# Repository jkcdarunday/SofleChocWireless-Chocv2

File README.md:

# Sofle Choc Wireless — Choc v2 Hole-Only

> **Untested hardware:** This modified PCB has not been physically tested.
> File-level checks do not verify switch fit, assembly, or electrical operation.
> Fabricate and build at your own risk; a working keyboard is not guaranteed.

| Left half (back view) | Right half (front view) |
| --- | --- |
|  |  |

Green bare-board KiCad 10 renders with component models hidden, arranged as
the assembled keyboard: left half on the left, right half on the right. The
reversible PCB uses its back face for the left half and front face for the
right half. SW25 is the isolated encoder/switch position below the reset button
in the right-half view.

Based on db-ok/SofleChocWireless at
`aae7cc0ac5ca563dab8222320ae8749ed1911e56`. This branch contains the adapted
board, matching source footprints and project settings, and fabrication files.

## Changes in this version

Enlarges all 30 switch-center NPTH holes from 3.4 mm to 5.0 mm, including SW25.
Reroutes affected connections around the enlarged center holes and uses
0.25 mm ground bridges where needed. No vias were added, removed, or moved.
No additional silent-switch pin relief is included in this version.

For switches requiring an additional locating-pin slot, see the
[Choc v2 Silent v2 branch](https://github.com/jkcdarunday/SofleChocWireless-Chocv2/tree/choc-v2-silent-v2),
which adds mirrored 1.5 × 2.0 mm non-plated slots at every switch position.

Both silkscreen labels credit `jkcdarunday` and the base design by `db`.
The schematic, electrical pad mapping, component placements, outline, LED
cutouts, mounting holes, firmware mapping, and case/plate geometry are preserved.

Open `SofleChocWireless/PCB/SofleKeyboard.kicad_pro` in KiCad 7 or newer.
The 30-position main board is reversible and serves either half.
`Gerbers/SofleChocWireless/SofleChocWireless.zip` contains this version's
main-board copper, masks, silkscreens, outline, and PTH/NPTH drills; the loose
exports match the archive. Plate exports remain unchanged upstream files.

## Validation and remaining limits

Saved KiCad 7.0.11 checks reported 400 findings before and after conversion,
with zero copper clearance violations and zero unconnected pads. Later
KiCad 9 checks also found no new electrical DRC issues in the conversion;
counts differ with engine, library resolution, and zone filling.

These are historical file-level results, not a new validation run or physical
qualification. Existing DRC findings remain. At SW25, the enlarged hole leaves
only a nominal 0.249 mm laminate web to the LED cutout. Confirm fabrication
capability and the actual switch/plate fit before ordering. No physical switch
fit, assembled-board, or power/temperature tests have been performed. The RGB
power arrangement is unchanged. Original license and attribution are retained.

## Upstream documentation

# Sofle Choc Wireless Keyboard

The Sofle Choc Wireless Keyboard is a revision of the Sofle Choc keyboard by [Brian Low](https://github.com/brianlow) with features that make it more suitable to building with wireless microcontrollers.

*The Sofle Choc Wireless Keyboard with an encoder and nice!view on the left half*

--
--

The following 2 pictures are the same exact board:

  *(Above: the Sofle Choc Wireless Keyboard with RGB LEDs and dual encoders)*

  *(Above: The Sofle Choc Wireless Keyboard with RGB LEDs and no encoders)*

The encoders in the first picture were hot-swapped for Choc switches in the second picture.
This allows for more build flexibility to change up your build, and as an added bonus, you can test out different rotary encoder options without soldering them in until you find one that you like.

## Disclaimer
This is a prototype keyboard, so it comes with no guarantees. There may be changes to it in the future to fix problems or add features. That being said, it functions as intended for my own standards, so if you like the design, feel free to get a PCB made and build it for yourself!

## Differences from Sofle Choc (wired) keyboard
- Added power switch to connect/disconnect battery power to RAW pin of microcontroller
- Added JST connector for battery connection
- [nice!view](https://nicekeyboards.com/docs/nice-view/) display support *(still supports common OLED displays as well)*
- Encoder can be swapped with a Choc switch on either half
    - These can both be hot-swapped if Mill-Max sockets are installed
- Added a bottom plate PCB to allow for more build options
- Made a hole in the PCB for battery wire routing if needed
- Position of the encoder is shifted down to allow room for a larger encoder knob
- 1 additional RBG LED on each half under the encoder / choc switch position
- Removed the TRRS jacks and related components
- Changed the microcontroller pin connected to the RGB LED data line

## Encoder Support
The PCB supports a rotary encoder or a Choc switch in the same location on either half, and *either one can use Mill-Max sockets*. If you don't want to use Mill-Max sockets, you can hard-solder either a rotary encoder or a Choc switch into either side.

## Display Support
The PCB supports either a 4-pin OLED screen commonly found on DIY keyboards, or the 5-pin [nice!view](https://nicekeyboards.com/docs/nice-view/) low power usage display.

## Firmware 

Sofle Choc Wireless uses [ZMK firmware](https://zmk.dev/)

Firmware-related info for display and LED features:
  - This PCB has a chip select (CS) pin for the nice!view display that uses Arduino Digital 1 (D1 Pro Micro pin), which corresponds to P0.06/006 on the nice!nano. This is the default pin used by the nice!view, which makes it easier to configure. See build guide "Firmware and programming" section for more info on building firmware that supports the nice!view.
  - The RGB LED pin is relocated to Arduino Digital 0 (D0 Pro Micro pin), which corresponds to P0.08/008 on the nice!nano

### Example config repository
There is a zmk-config example repository where each branch has a different combination of options (OLED, niceview, RGB) enabled:
https://github.com/db-ok/zmk-config-soflechocwireless

## Build Guide

Please read the entire build guide before ordering any parts, as there are some options to consider:

[Build guide](docs/build_guide_choc_wireless.md)

## From the original Sofle repo:

Original SofleKeyboard repo: https://github.com/josefadamcik/SofleKeyboard

Sofle is 6×4+5 keys column-staggered split keyboard with encoder support. 

Based on [Lily58](https://github.com/kata0510/Lily58), [Corne](https://github.com/foostan/crkbd) and [Helix](https://github.com/MakotoKurauchi/helix) keyboards.

SofleKeyboard was created by [Josef Adamcik](https://josef-adamcik.cz/). The motivation and process is covered in following blog-post: [Let me introduce you to SofleKeyboard - a split keyboard based on Lily58 and Crkbd](https://josef-adamcik.cz/electronics/let-me-introduce-you-sofle-keyboard-split-keyboard-based-on-lily58.html)

Sofle RGB was contributed by [Dane Evans](https://github.com/DaneEvans).

Sofle Choc was designed by [Brian Low](https://github.com/BrianLow)

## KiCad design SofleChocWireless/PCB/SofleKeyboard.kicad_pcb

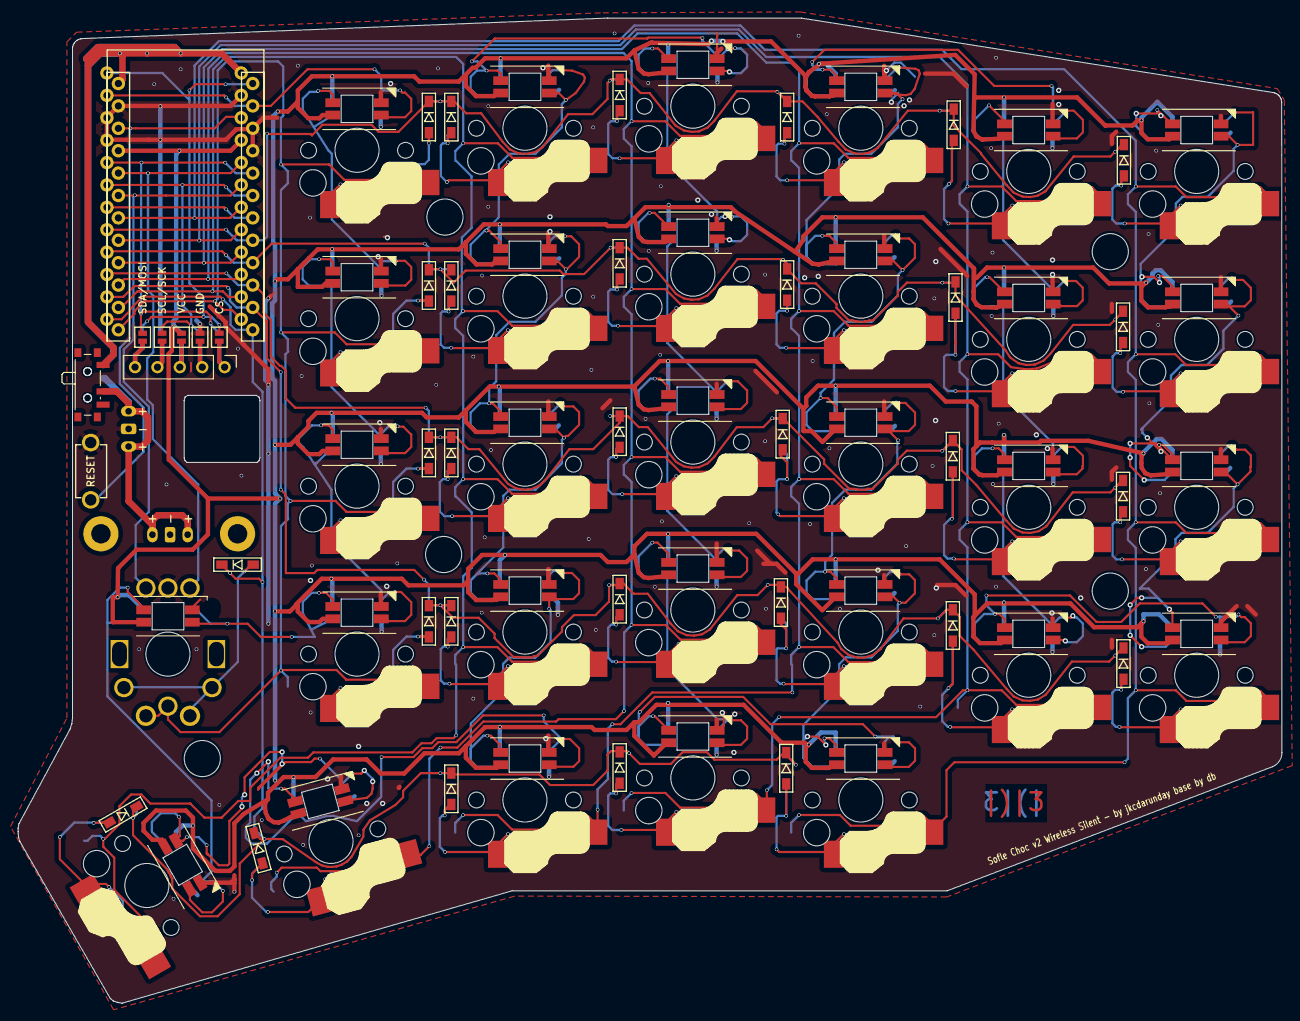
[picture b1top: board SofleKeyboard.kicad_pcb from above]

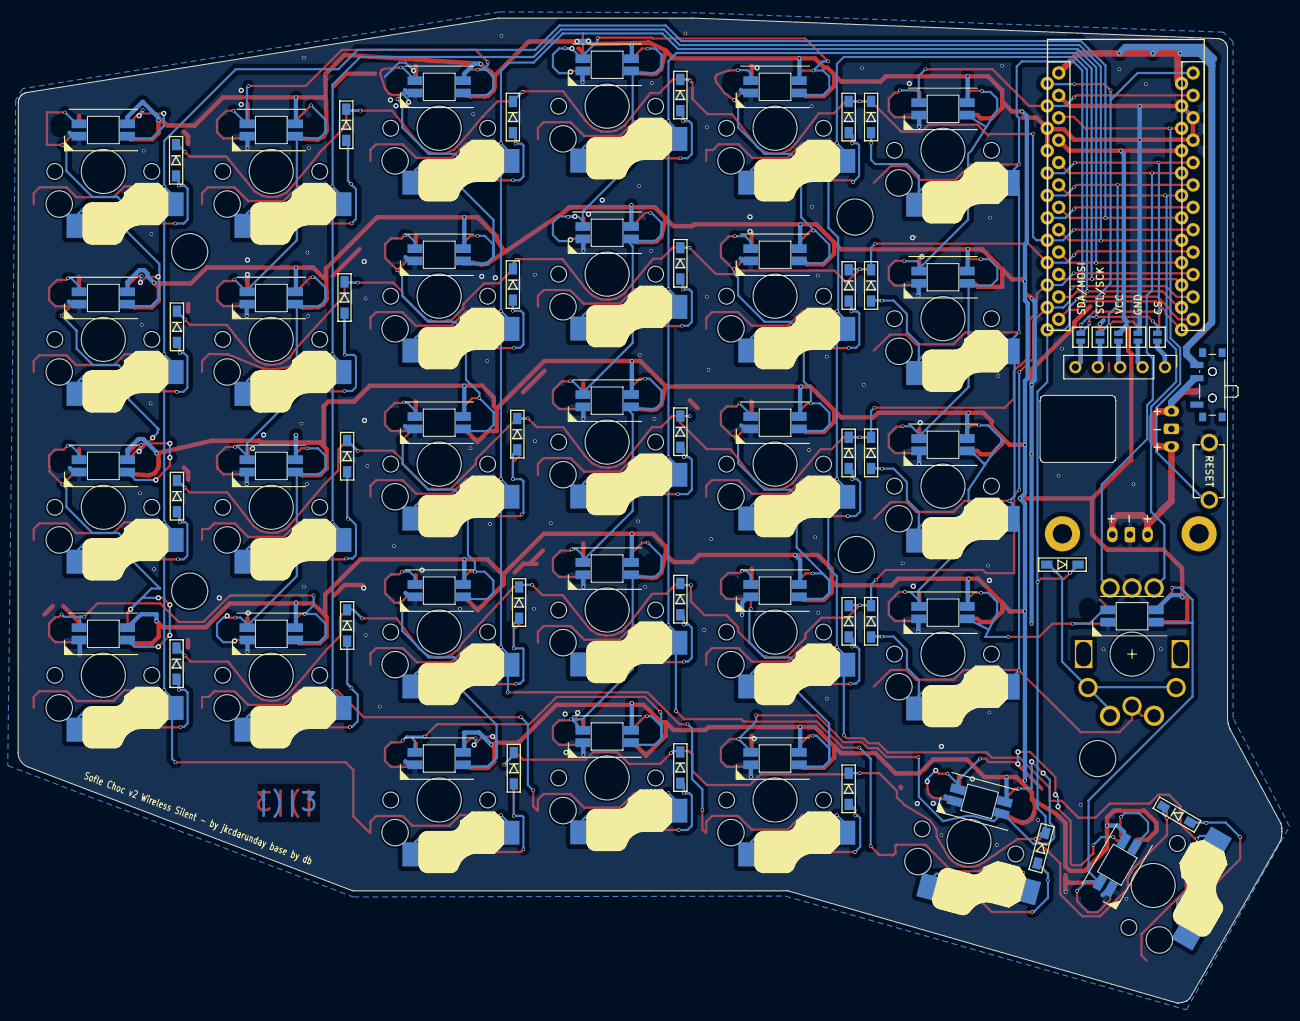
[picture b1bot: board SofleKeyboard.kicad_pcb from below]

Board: 2 copper layers, 143.4 x 111.8 mm, 85 parts (6 on the bottom side), 86 nets.

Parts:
D1, D2, D3, D4, D5, D6, D7, D8, D9, D10, D11, D12, D13, D14, D15, D16, D17, D18, D19, D20, D21, D22, D23, D24, D25, D26, D27, D28, D29, D30: D; crkbd-diode
J3: OLED; OLED_NICEVIEW_COMBO_HDR_5Pin
JP0, JP1, JP2, JP3, JP4, JP5, JP6, JP7, JP8, JP9: Jumper_NO_Small; Jumper_small
JST_BATT1, JST_BATT2: Conn_01x02; JST_PH_S2B-PH-K_1x02_P2.00mm_DoubleSided
RSW1: SW_RST; TACT_SWITCH_TVBP06
SW1, SW7, SW13, SW19: SW_PUSH_LED; Choc_Hotswap_SK6812MiniE_BiggerHSPads_Column1
SW2, SW3, SW4, SW5, SW6, SW8, SW9, SW10, SW11, SW12, SW14, SW15, SW16, SW17, SW18, SW20, SW21, SW22, SW23, SW24, SW26, SW27, SW28, SW29, SW30: SW_PUSH_LED; Choc_Hotswap_SK6812MiniE_BiggerHSPads
SW25: SW_PUSH_LED; Kailh-PG1350-1u-reversible-SK6812MiniE_MODIFIED
SW31: Rotary_Encoder_Switch; RotaryEncoder_Alps_EC11E-Switch_Vertical_H20mm-keebio_modif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
SW_BATT+1, SW_BATT+2: SW_SPST; SW_SPDT_PCM12
TH1, TH2: HOLE; M2_HOLE_PCB
TH3, TH4, TH5, TH6, TH7: HOLE; HOLE_M2_TH
U1: ProMicro

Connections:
CS: JP0.2, JP9.2, U1.1 (TX(PD3))
ENCA: SW31.A, U1.20 (A3(PF4))
ENCB: SW31.B, U1.19 (A2(PF5))
GND: JP1.2, JP8.2, JST_BATT1.1, JST_BATT2.1, RSW1.1, SW1.3 (GND), SW2.3 (GND), SW3.3 (GND), SW4.3 (GND), SW5.3 (GND), SW6.3 (GND), SW7.3 (GND), SW8.3 (GND), SW9.3 (GND), SW10.3 (GND), SW11.3 (GND), SW12.3 (GND), SW13.3 (GND), SW14.3 (GND), SW15.3 (GND), SW16.3 (GND), SW17.3 (GND), SW18.3 (GND), SW19.3 (GND), SW20.3 (GND), SW21.3 (GND), SW22.3 (GND), SW23.3 (GND), SW24.3 (GND), SW25.3 (GND), SW26.3 (GND), SW27.3 (GND), SW28.3 (GND), SW29.3 (GND), SW30.3 (GND), SW31.C, U1.3 (GND), U1.4 (GND), U1.23 (GND)
LED: SW1.4 (DIN), U1.2 (RX(PD2))
unnamed: D1.2 (A), SW1.5
unnamed: D2.2 (A), SW2.5
unnamed: D3.2 (A), SW3.5
unnamed: D4.2 (A), SW4.5
unnamed: D5.2 (A), SW5.5
unnamed: D6.2 (A), SW6.5
unnamed: D7.2 (A), SW7.5
unnamed: D8.2 (A), SW8.5
unnamed: D9.2 (A), SW9.5
unnamed: D10.2 (A), SW10.5
unnamed: D11.2 (A), SW11.5
unnamed: D12.2 (A), SW12.5
unnamed: D13.2 (A), SW13.5
unnamed: D14.2 (A), SW14.5
unnamed: D15.2 (A), SW15.5
unnamed: D16.2 (A), SW16.5
unnamed: D17.2 (A), SW17.5
unnamed: D18.2 (A), SW18.5
unnamed: D19.2 (A), SW19.5
unnamed: D20.2 (A), SW20.5
unnamed: D21.2 (A), SW21.5
unnamed: D22.2 (A), SW22.5
unnamed: D23.2 (A), SW23.5
unnamed: D24.2 (A), SW24.5
unnamed: D25.2 (A), SW25.6, SW31.S2
unnamed: D26.2 (A), SW26.5
unnamed: D27.2 (A), SW27.5
unnamed: D28.2 (A), SW28.5
unnamed: D29.2 (A), SW29.5
unnamed: D30.2 (A), SW30.5
unnamed: J3.1, JP4.1, JP9.1
unnamed: J3.2, JP3.1, JP8.1
unnamed: J3.3, JP2.1, JP7.1
unnamed: J3.4, JP1.1, JP6.1
unnamed: J3.5, JP0.1, JP5.1
unnamed: JST_BATT1.2, JST_BATT2.2, SW_BATT+1.2 (B), SW_BATT+2.2 (B)
unnamed: SW1.2 (DOUT), SW7.4 (DIN)
unnamed: SW2.2 (DOUT), SW3.4 (DIN)
unnamed: SW2.4 (DIN), SW8.2 (DOUT)
unnamed: SW3.2 (DOUT), SW9.4 (DIN)
unnamed: SW4.2 (DOUT), SW5.4 (DIN)
unnamed: SW4.4 (DIN), SW10.2 (DOUT)
unnamed: SW10.4 (DIN), SW16.2 (DOUT)
unnamed: SW11.2 (DOUT), SW17.4 (DIN)
unnamed: SW5.2 (DOUT), SW11.4 (DIN)
unnamed: SW6.4 (DIN), SW12.2 (DOUT)
unnamed: SW12.4 (DIN), SW18.2 (DOUT)
unnamed: SW13.2 (DOUT), SW19.4 (DIN)
unnamed: SW7.2 (DOUT), SW13.4 (DIN)
unnamed: SW8.4 (DIN), SW14.2 (DOUT)
unnamed: SW14.4 (DIN), SW20.2 (DOUT)
unnamed: SW15.2 (DOUT), SW21.4 (DIN)
unnamed: SW9.2 (DOUT), SW15.4 (DIN)
unnamed: SW16.4 (DIN), SW22.2 (DOUT)
unnamed: SW17.2 (DOUT), SW23.4 (DIN)
unnamed: SW18.4 (DIN), SW24.2 (DOUT)
unnamed: SW19.2 (DOUT), SW25.4 (DIN)
unnamed: SW20.4 (DIN), SW28.2 (DOUT)
unnamed: SW21.2 (DOUT), SW29.4 (DIN)
unnamed: SW22.4 (DIN), SW30.2 (DOUT)
unnamed: SW23.2 (DOUT), SW24.4 (DIN)
unnamed: SW25.2 (DOUT), SW26.4 (DIN)
unnamed: SW26.2 (DOUT), SW27.4 (DIN)
unnamed: SW27.2 (DOUT), SW28.4 (DIN)
unnamed: SW29.2 (DOUT), SW30.4 (DIN)
unnamed: SW_BATT+1.1 (A), SW_BATT+2.1 (A), U1.24 (RAW)
RESET: RSW1.2, U1.22 (RST)
SCL: JP3.2, JP6.2, U1.6 (SCL(PD0))
SDA: JP4.2, JP5.2, U1.5 (SDA(PD1))
VCC: JP2.2, JP7.2, SW1.1 (VDD), SW2.1 (VDD), SW3.1 (VDD), SW4.1 (VDD), SW5.1 (VDD), SW6.1 (VDD), SW7.1 (VDD), SW8.1 (VDD), SW9.1 (VDD), SW10.1 (VDD), SW11.1 (VDD), SW12.1 (VDD), SW13.1 (VDD), SW14.1 (VDD), SW15.1 (VDD), SW16.1 (VDD), SW17.1 (VDD), SW18.1 (VDD), SW19.1 (VDD), SW20.1 (VDD), SW21.1 (VDD), SW22.1 (VDD), SW23.1 (VDD), SW24.1 (VDD), SW25.1 (VDD), SW26.1 (VDD), SW27.1 (VDD), SW28.1 (VDD), SW29.1 (VDD), SW30.1 (VDD), U1.21 (VCC)
col0: SW6.6, SW12.6, SW18.6, SW24.6, SW30.6, U1.18 (A1(PF6))
col1: SW5.6, SW11.6, SW17.6, SW23.6, SW29.6, U1.17 (A0(PF7))
col2: SW4.6, SW10.6, SW16.6, SW22.6, SW28.6, U1.16 (D15(PB1))
col3: SW3.6, SW9.6, SW15.6, SW21.6, SW27.6, U1.15 (D14(PB3))
col4: SW2.6, SW8.6, SW14.6, SW20.6, SW26.6, U1.14 (D16(PB2))
col5: SW1.6, SW7.6, SW13.6, SW19.6, SW25.5, SW31.S1, U1.13 (D10(PB6))
row0: D1.1 (K), D2.1 (K), D3.1 (K), D4.1 (K), D5.1 (K), D6.1 (K), U1.8 (D5(PC6))
row1: D7.1 (K), D8.1 (K), D9.1 (K), D10.1 (K), D11.1 (K), D12.1 (K), U1.9 (D6(PD7))
row2: D13.1 (K), D14.1 (K), D15.1 (K), D16.1 (K), D17.1 (K), D18.1 (K), U1.10 (D7(PE6))
row3: D19.1 (K), D20.1 (K), D21.1 (K), D22.1 (K), D23.1 (K), D24.1 (K), U1.11 (D8(PB4))
row4: D25.1 (K), D26.1 (K), D27.1 (K), D28.1 (K), D29.1 (K), D30.1 (K), U1.12 (D9(PB5))
